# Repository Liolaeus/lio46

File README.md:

# Lio46 V2

Lio46 is a wireless, 46 key keyboard with my personal best layout in mind.  

# Notable features
- Wireless split keyboad
- 46 keys (23 per side), 4 thumb keys, one extra key on ring column
- Hot-swappable low profile kailh choc v1 switches
- Column staggered with aggressive pinky stagger
- Powered by [ZMK](https://zmk.dev/)
- Generated with [ergogen](https://github.com/ergogen/ergogen) 

more pictures [here](https://github.com/Liolaeus/lio46/tree/master/pictures) !

# V2 Changelog
- Removed underglow and backlight leds for better battery life
- Moved the thumb keys inwards
- Manual routing
- Fixed logo placement on the pcb
- Moved srew/standoff holes
- Trimmed edges of pcb
- Moved battery connector
- Added a case
- Moved key and display pins
- Supports E-ink nice view displays

# Firmware
You can find and modify the ZMK firmware for this keybaord [here](https://github.com/Liolaeus/lio46-zmk-config).

# Requirements
If you want to modify this keyboard here is the list of software dependencies to run all the scripts in this repository:

- GNU make
- ergogen
- kicad 8
- docker
- python

# Parts
If you want to build this keyboard, you can find all the parts [here](https://github.com/Liolaeus/lio46/blob/master/parts.md)

# References
A list of projects and tools that were used and/or taken inspiration from for the creation of this project, many thanks to all of them.

- [ZMK Firmware](https://zmk.dev/)
- [Sofle ZMK config](https://github.com/zmkfirmware/zmk/tree/0820991901a95ab7a0eb1f1cc608a631d514e26c/app/boards/shields/sofle)
- [Ergogen](https://github.com/ergogen/ergogen)
- [Freerouting](https://github.com/freerouting/freerouting)
- [Flatfootfox blog](https://flatfootfox.com/ergogen-part1-units-points/)
- [SpUnLy58 keyboard](https://github.com/Giraffasax/SpUnLy58/tree/main)
- [Corney-island keyboard](https://github.com/ceoloide/corney-island)
- [NostrumX keyboard](https://github.com/bennytrouser/NostrumX/tree/main)
- [Caldera keyboard](https://github.com/christianselig/caldera-keyboard/tree/main)
- [Avalanche keyboard](https://github.com/vlkv/avalanche/tree/master)

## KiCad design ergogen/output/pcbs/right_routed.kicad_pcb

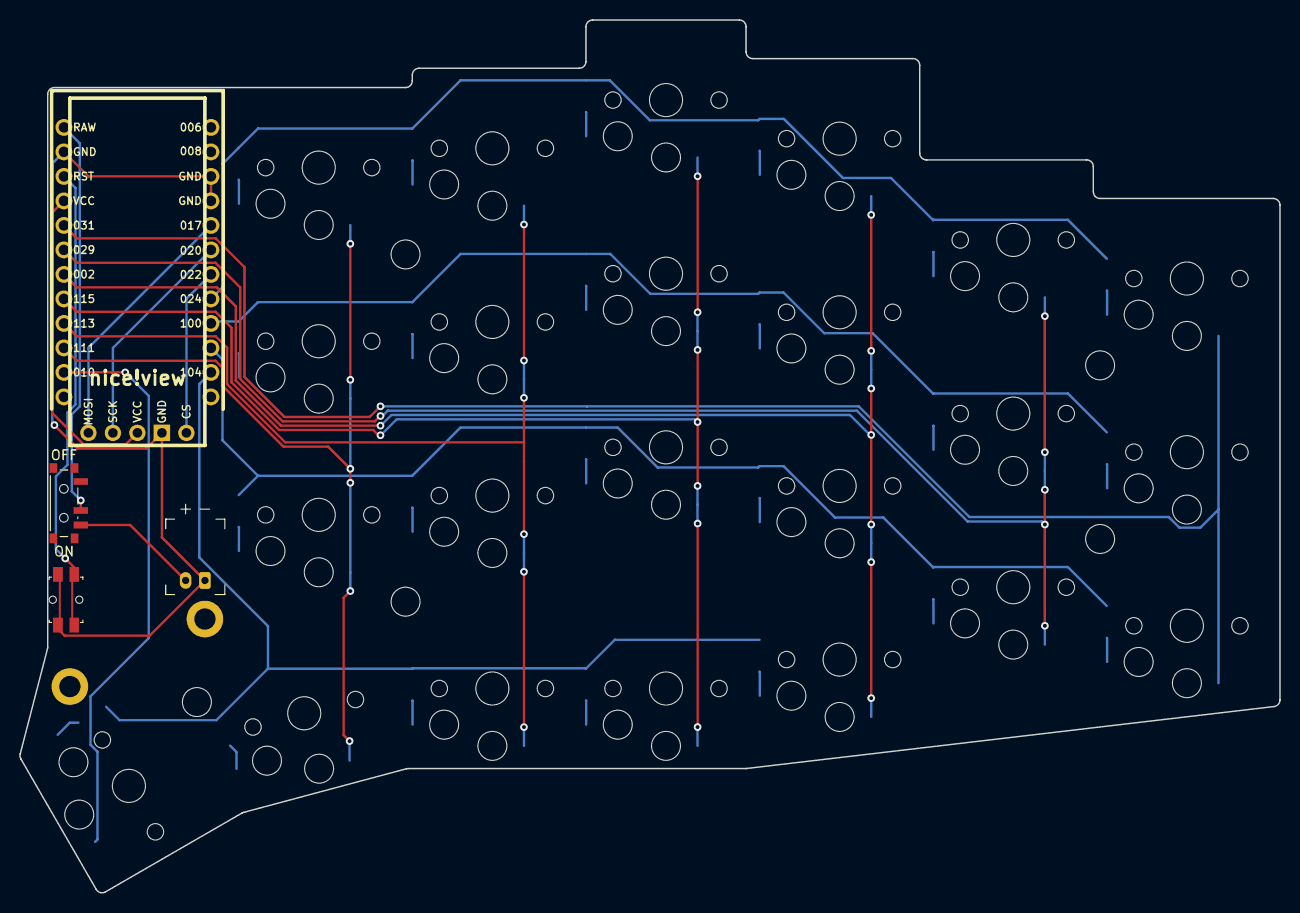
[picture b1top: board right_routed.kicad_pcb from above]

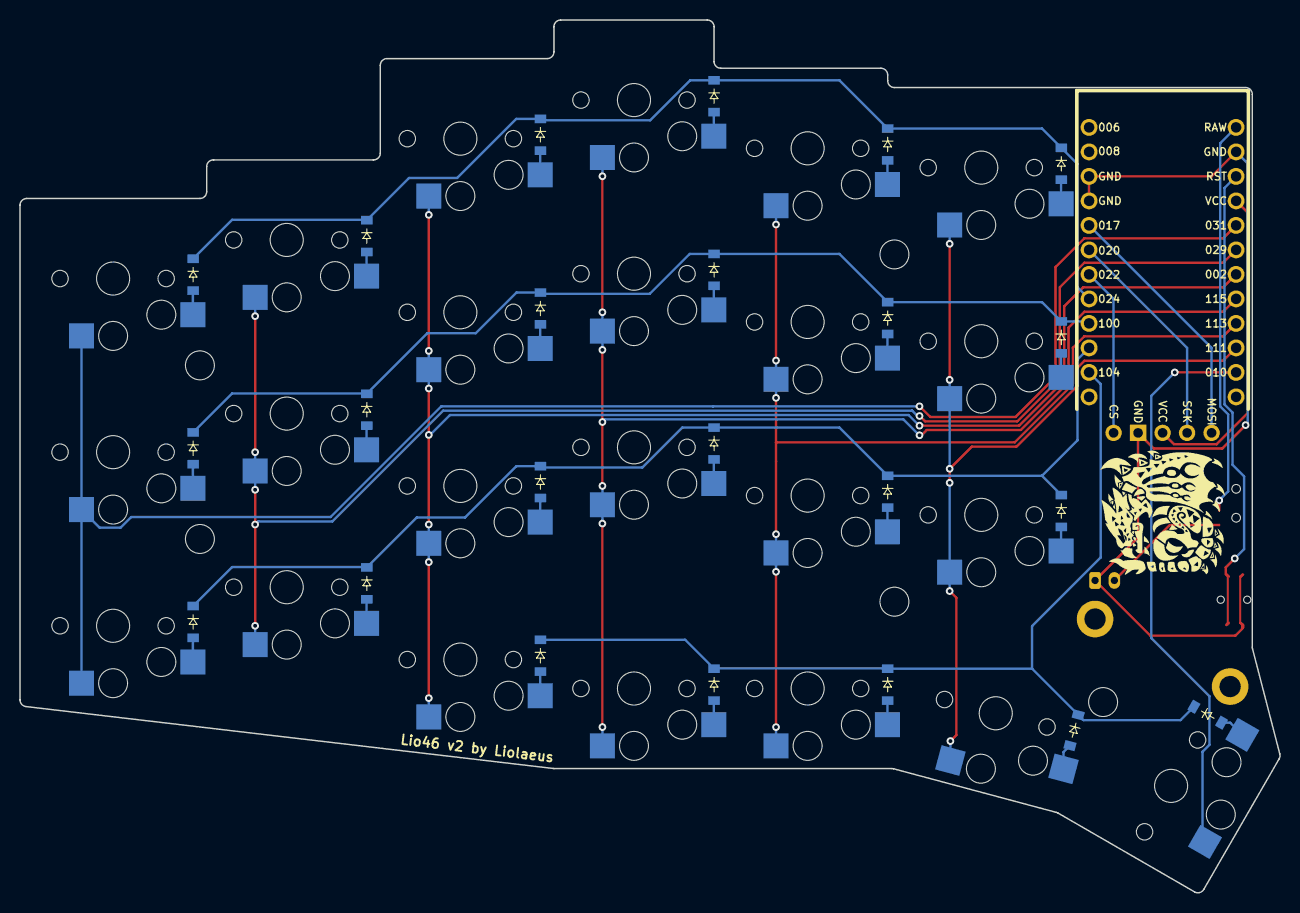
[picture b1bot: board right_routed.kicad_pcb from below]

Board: 2 copper layers, 130.6 x 90.5 mm, 59 parts (24 on the bottom side), 42 nets.

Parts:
D1, D2, D3, D4, D5, D6, D7, D8, D9, D10, D11, D12, D13, D14, D15, D16, D17, D18, D19, D20, D21, D22, D23: diode_tht_sod123
G: LOGO; lio
H1, H2: mounting_hole_plated
JST1: battery_connector_jst_ph_2
MCU1: nice_nano
MH1, MH2, MH3, MH4, MH5: mounting_hole_npth
PWR1: power_switch_smd_side
RST1: reset_switch_smd_side
S1, S2, S3, S4, S5, S6, S7, S8, S9, S10, S11, S12, S13, S14, S15, S16, S17, S18, S19, S20, S21, S22, S23: PG1350
niceView1: niceView; niceView_headers

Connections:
BAT_P: JST1.2, PWR1.3
GND: JST1.1, MCU1.3, MCU1.4, MCU1.23, RST1.1, RST1.3, niceView1.2
P002: MCU1.18, S7.1, S8.1, S9.1, S10.1
P010: MCU1.14, S23.1
P011: D1.1, D4.1, D8.1, D11.1, D14.1, D17.1, MCU1.10
P017: MCU1.5, niceView1.5
P020: MCU1.6, niceView1.4
P022: MCU1.7, niceView1.1
P024: D3.1, D6.1, D10.1, D13.1, D16.1, D19.1, MCU1.8
P029: MCU1.19, S4.1, S5.1, S6.1
P031: MCU1.20, S1.1, S2.1, S3.1
P100: D2.1, D5.1, D9.1, D12.1, D15.1, D18.1, MCU1.9
P104: D7.1, D20.1, D21.1, D22.1, D23.1, MCU1.11
P111: MCU1.15, S17.1, S18.1, S19.1, S22.1
P113: MCU1.16, S14.1, S15.1, S16.1, S21.1
P115: MCU1.17, S11.1, S12.1, S13.1, S20.1
RAW: MCU1.24, PWR1.2
RST: MCU1.22, RST1.2, RST1.4
VCC: MCU1.21, niceView1.3
mirror_close_thumb: D21.2, S21.2
mirror_home_thumb: D22.2, S22.2
mirror_index_bottom: D14.2, S14.2
mirror_index_home: D15.2, S15.2
mirror_index_top: D16.2, S16.2
mirror_inner_bottom: D17.2, S17.2
mirror_inner_home: D18.2, S18.2
mirror_inner_thumb: D20.2, S20.2
mirror_inner_top: D19.2, S19.2
mirror_middle_bottom: D11.2, S11.2
mirror_middle_home: D12.2, S12.2
mirror_middle_top: D13.2, S13.2
mirror_outer_bottom: D1.2, S1.2
mirror_outer_home: D2.2, S2.2
mirror_outer_thumb: D23.2, S23.2
mirror_outer_top: D3.2, S3.2
mirror_pinky_bottom: D4.2, S4.2
mirror_pinky_home: D5.2, S5.2
mirror_pinky_top: D6.2, S6.2
mirror_ring_bonus: D7.2, S7.2
mirror_ring_bottom: D8.2, S8.2
mirror_ring_home: D9.2, S9.2
mirror_ring_top: D10.2, S10.2

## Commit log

2024-10-15 add: ergogen config and footprints
2024-10-18 fix: button positions
2024-10-20 add: component placement, niceview, mirror pcb
2024-10-22 fix: ergogen lio logo
2024-11-03 add: routing paras, position adjustments
2024-11-12 add: ignore venv files
2024-11-12 add: freerouting docker image
2024-11-12 add: python freerouting utils
2024-11-12 update: references
2024-11-12 update: nice_view pins
2024-11-12 add: makefile
2024-11-15 fix: improvements on auto routing workflow
2024-11-15 fix: diode / hole / led placement
2024-11-15 update: readme desc, issues, references
2024-11-16 fix: remove venv
2024-11-16 add: via cost
2024-11-16 fix: thumbfan row/cols
2024-11-16 add: requirements and references
2024-11-16 add: generated files
2024-11-16 add: readme pictures and description
2024-11-16 add: gerber files
2024-11-16 fix: capitalization
2024-11-16 fix: mention rgb
2024-11-17 add: init zmk config
2024-12-07 add: documentation
2024-12-07 add: parts link
2024-12-07 fix: part links
2024-12-07 fix: part number
2024-12-07 fix: remove workflows
2024-12-07 add: v1 pictures
2024-12-11 add: rebuild ergogen on footprint modification
2024-12-11 add: zmk config
2024-12-11 fix: west conf path
2024-12-11 fix: remove zmk conf
2024-12-11 fix: keyboard name
2024-12-11 wip: v2
2024-12-14 wip: unrouted v2
2024-12-14 fix: remove github acitons
2024-12-15 wip: right routed
2024-12-16 wip: change nice view pins / reroute
2024-12-18 add: v2 gerbers
2025-01-01 add: case / switchplate
2025-01-05 add: case files
2025-01-25 update: readme / parts
2025-01-25 update: case
2025-01-25 update: keyboard pictures
2025-01-27 add: more pictures
2025-01-28 fix: readme typo
